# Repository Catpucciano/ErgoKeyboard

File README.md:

<h1 align="center">Catpucciano</h1>

Catpucciano is 34 key key column-staggered choc split keyboard using a SEEED XIAO BLE and inspired by [TOTEM](https://github.com/GEIGEIGEIST/TOTEM/tree/main)

\

---

## Layout

---

## BUILD GUIDE

---

## FILES

### PCB
Gerber Files [Here](/docs/PCB/)
- Download the two zip files and upload them to your choice of manufacture. I used [JLCPCB](https://jlcpcb.com/)
### CASE
Printed in two sections with FDM Printer <br>
3mf for all three files [Case](<./docs/Case Files/Case.3mf>) <br>
[Case](<./docs/Case Files/Case.stl>) <br>
[Top](<./docs/Case Files/Top Case.stl>) <br>
[Top with imbedded Magnets](<./docs/Case Files/Top Magnet.stl>) <br>
[Tenting Case 45 Degrees](<./docs/Case Files/Tenting Case 45.stl>) <br>

---

## FIRMWARE

---

## Credits

### I like the [TOTEM](https://github.com/GEIGEIGEIST/TOTEM/tree/main) by GEIST but not a fan of the splayed layout and wanted something more compact. Having the thumb cluster angled also makes it somewhat awkaward with it sticking out. I removed the upper corner keys to make the keyboard as small as possible to maximize desk space and portability.

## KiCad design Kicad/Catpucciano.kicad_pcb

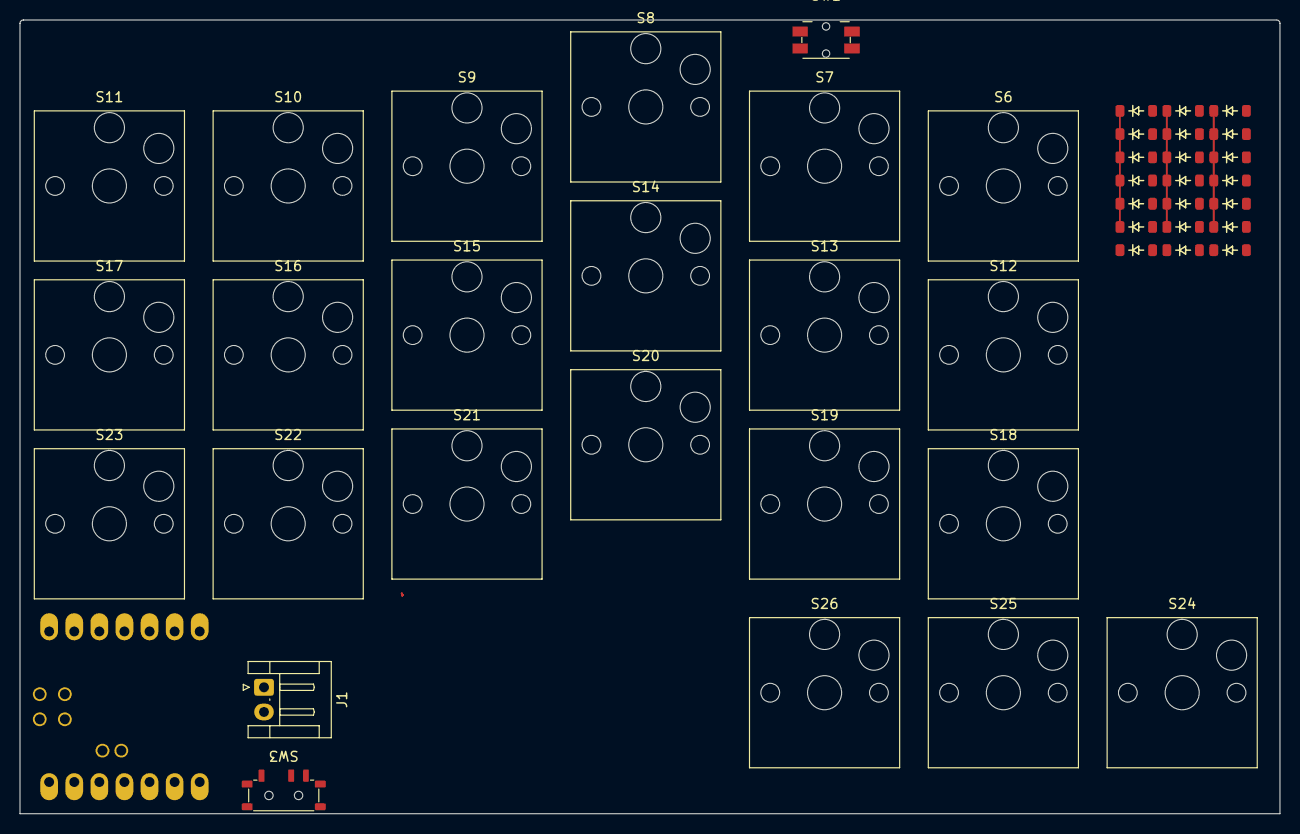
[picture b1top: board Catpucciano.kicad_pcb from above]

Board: 2 copper layers, 127.6 x 80.4 mm, 46 parts (0 on the bottom side), 35 nets.

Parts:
D6, D7, D8, D9, D10, D11, D12, D13, D14, D15, D16, D17, D18, D19, D20, D21, D22, D23, D24, D25, D26: Diode; Diode_SOD-123
J1: Conn_01x02; JST_EH_S2B-EH_1x02_P2.50mm_Horizontal
S6, S7, S8, S9, S10, S11, S12, S13, S14, S15, S16, S17, S18, S19, S20, S21, S22, S23, S24, S25, S26: Keyswitch; Hotswap_Choc_V1_1.00u
SW1: RSW; Panasonic_EVQPUL_EVQPUC
SW3: Switch; Switch_MSK12C02
xiao-ble1: U; xiao-ble-tht

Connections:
BAT+: SW3.1, xiao-ble1.19 (BAT+)
COL0: S6.1, S12.1, S18.1, S24.1, xiao-ble1.6 (A5/05/SCL)
COL1: S7.1, S13.1, S19.1, S25.1, xiao-ble1.7 (Tx/11)
COL2: S8.1, S14.1, S20.1, S26.1, xiao-ble1.8 (Rx/12)
COL3: S9.1, S15.1, S21.1, xiao-ble1.9 (SCK/13)
COL4: S10.1, S16.1, S22.1, xiao-ble1.10 (MISO/14)
COL5: S11.1, S17.1, S23.1, xiao-ble1.11 (MOSI/15)
GND: J1.1, SW1.2, xiao-ble1.13 (GND), xiao-ble1.18 (GND), xiao-ble1.20 (GND)
unnamed: D6.2 (A), S6.2
unnamed: D7.2 (A), S7.2
unnamed: D8.2 (A), S8.2
unnamed: D9.2 (A), S9.2
unnamed: D10.2 (A), S10.2
unnamed: D11.2 (A), S11.2
unnamed: D12.2 (A), S12.2
unnamed: D13.2 (A), S13.2
unnamed: D14.2 (A), S14.2
unnamed: D15.2 (A), S15.2
unnamed: D16.2 (A), S16.2
unnamed: D17.2 (A), S17.2
unnamed: D18.2 (A), S18.2
unnamed: D19.2 (A), S19.2
unnamed: D20.2 (A), S20.2
unnamed: D21.2 (A), S21.2
unnamed: D22.2 (A), S22.2
unnamed: D23.2 (A), S23.2
unnamed: D24.2 (A), S24.2
unnamed: D25.2 (A), S25.2
unnamed: D26.2 (A), S26.2
RESET: SW1.1, xiao-ble1.17 (RST)
ROW1: D6.1 (K), D7.1 (K), D8.1 (K), D9.1 (K), D10.1 (K), D11.1 (K), xiao-ble1.2 (A1/03)
ROW2: D12.1 (K), D13.1 (K), D14.1 (K), D15.1 (K), D16.1 (K), D17.1 (K), xiao-ble1.3 (A2/28)
ROW3: D18.1 (K), D19.1 (K), D20.1 (K), D21.1 (K), D22.1 (K), D23.1 (K), xiao-ble1.4 (A3/29)
ROW4: D24.1 (K), D25.1 (K), D26.1 (K), xiao-ble1.5 (A4/04/SDA)
VBAT: J1.2, SW3.2

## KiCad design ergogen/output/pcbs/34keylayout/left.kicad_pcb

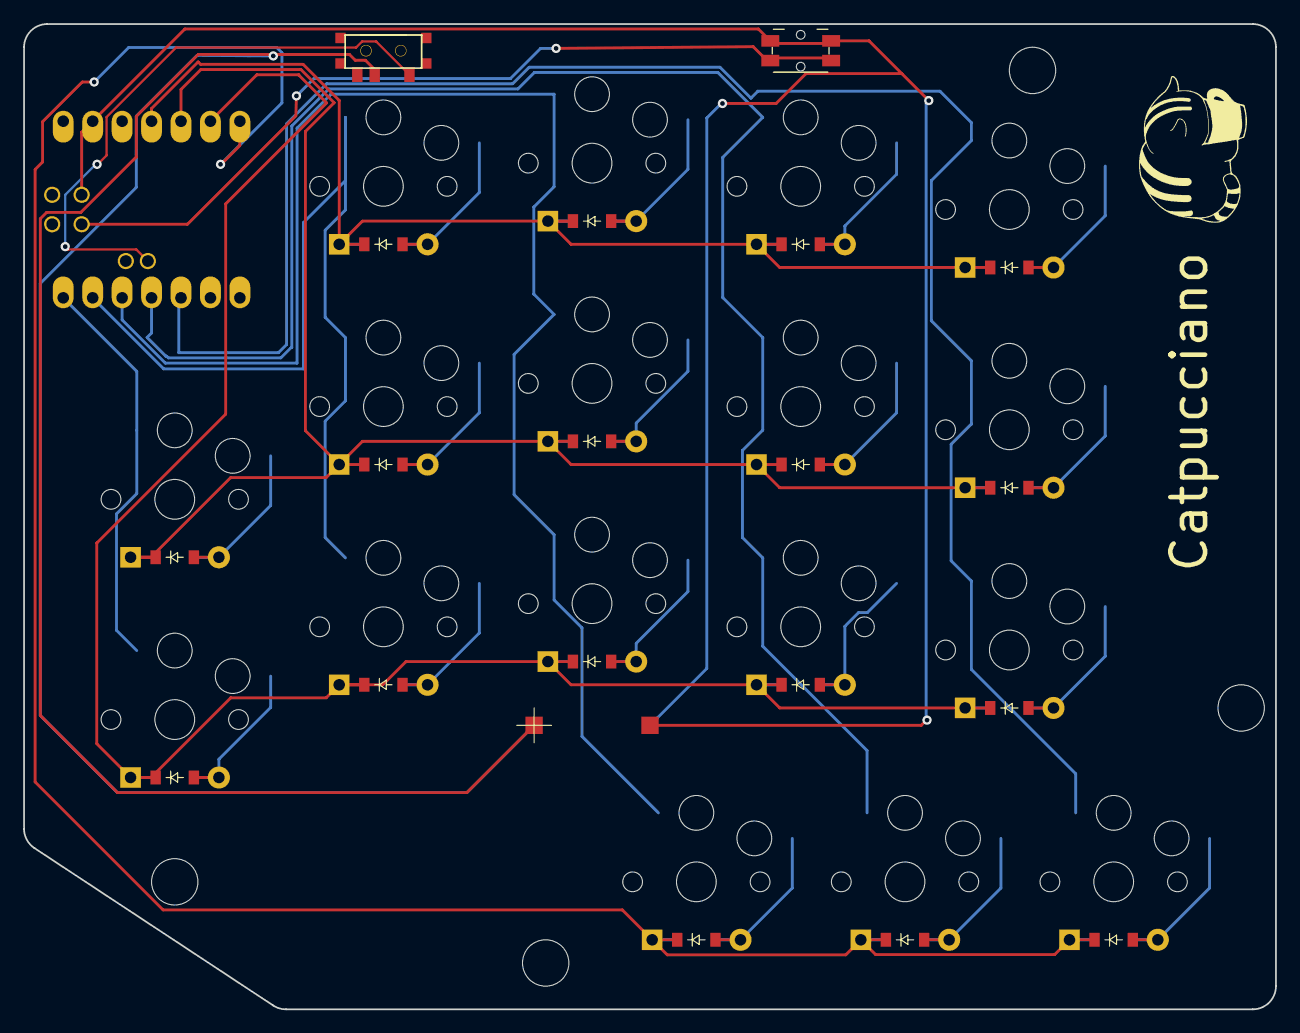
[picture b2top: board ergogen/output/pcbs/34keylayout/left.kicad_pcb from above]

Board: 2 copper layers, 108.0 x 85.0 mm, 38 parts (0 on the bottom side), 30 nets.

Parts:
B1: Panasonic_EVQPUL_EVQPUC
BATTPAD1: ComboDiode
D1, D2, D3, D4, D5, D6, D7, D8, D9, D10, D11, D12, D13, D14, D15, D16, D17: ComboDiode
MCU1: xiao-ble
S1, S2, S3, S4, S5, S6, S7, S8, S9, S10, S11, S12, S13, S14, S15, S16, S17: PG1350
T1: SPDT_C128955

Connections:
BAT+: MCU1.18, T1.1
GND: B1.1, BATTPAD1.2, MCU1.12, MCU1.16
P0: MCU1.6, S1.1, S2.1
P1: MCU1.5, S3.1, S4.1, S5.1
P2: MCU1.4, S6.1, S7.1, S8.1, S15.1
P3: MCU1.3, S9.1, S10.1, S11.1, S16.1
P4: MCU1.2, S12.1, S13.1, S14.1, S17.1
P7: D15.1, D16.1, D17.1, MCU1.7
P8: D1.1, D3.1, D6.1, D9.1, D12.1, MCU1.8
P9: D2.1, D4.1, D7.1, D10.1, D13.1, MCU1.9
P10: D5.1, D8.1, D11.1, D14.1, MCU1.10
POS: BATTPAD1.1, T1.2
RST: B1.2, MCU1.17
index_bottom: D9.2, S9.2
index_clusters: D16.2, S16.2
index_middle: D10.2, S10.2
index_top: D11.2, S11.2
inner_bottom: D12.2, S12.2
inner_clusters: D17.2, S17.2
inner_middle: D13.2, S13.2
inner_top: D14.2, S14.2
middle_bottom: D6.2, S6.2
middle_clusters: D15.2, S15.2
middle_middle: D7.2, S7.2
middle_top: D8.2, S8.2
pinky_bottom: D1.2, S1.2
pinky_middle: D2.2, S2.2
ring_bottom: D3.2, S3.2
ring_middle: D4.2, S4.2
ring_top: D5.2, S5.2

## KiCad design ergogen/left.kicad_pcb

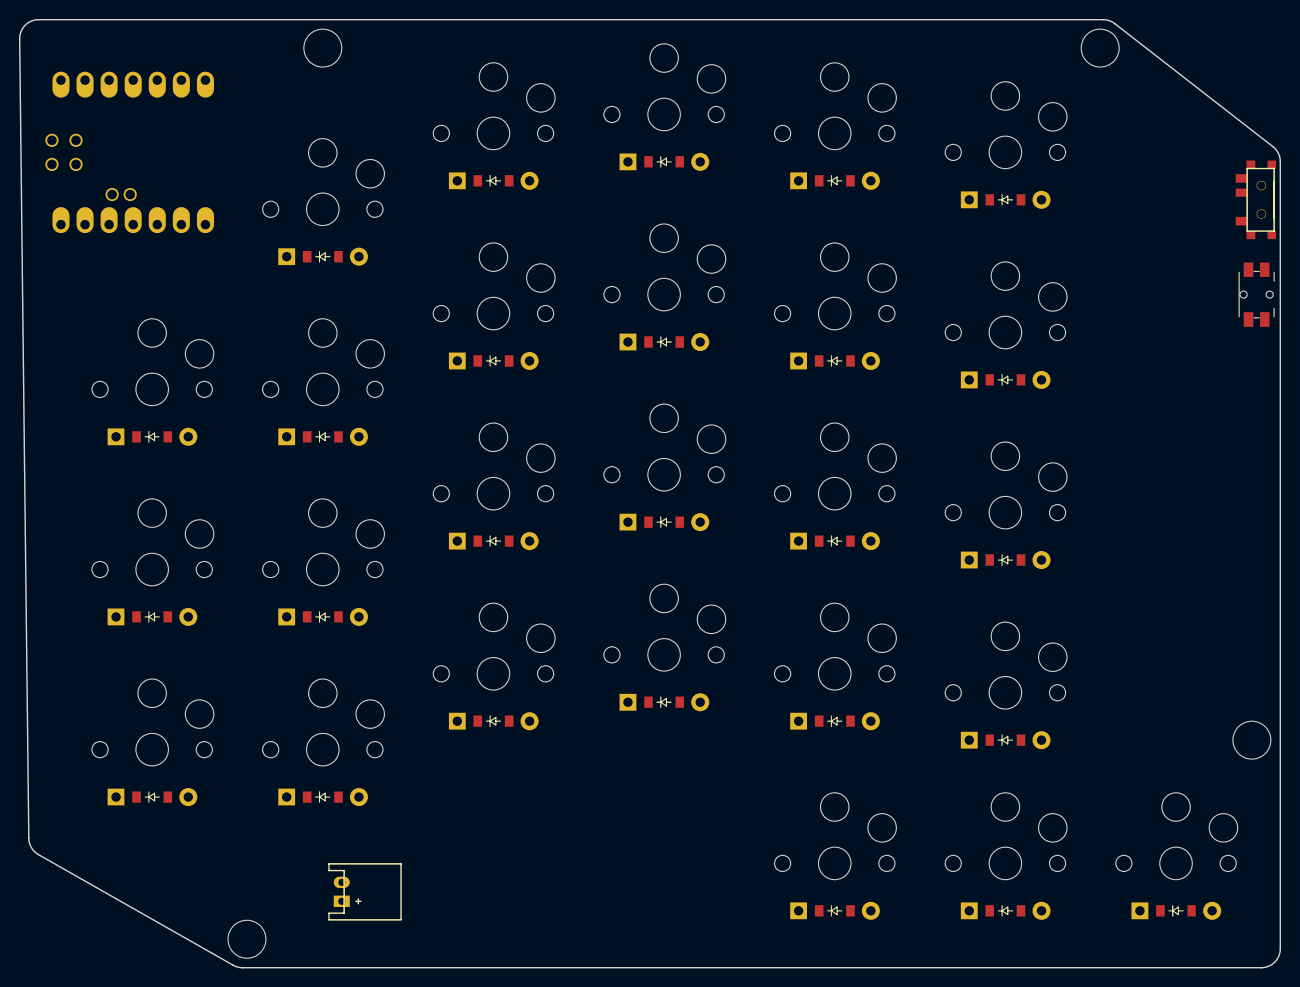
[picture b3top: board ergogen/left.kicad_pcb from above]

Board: 2 copper layers, 133.0 x 100.0 mm, 56 parts (0 on the bottom side), 6 nets, no tracks yet.

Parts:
B1: Panasonic_EVQPUL_EVQPUC
D1, D2, D3, D4, D5, D6, D7, D8, D9, D10, D11, D12, D13, D14, D15, D16, D17, D18, D19, D20, D21, D22, D23, D24, D25, D26: ComboDiode
JST1: JST_PH_S2B-PH-K_02x2.00mm_Angled
MCU1: xiao-ble
S1, S2, S3, S4, S5, S6, S7, S8, S9, S10, S11, S12, S13, S14, S15, S16, S17, S18, S19, S20, S21, S22, S23, S24, S25, S26: PG1350
T1: SPDT_C128955

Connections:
GND: B1.1, JST1.2, MCU1.2, MCU1.17, T1.2
P6: D24.1, D25.1, D26.1, MCU1.8
P7: D1.1, D4.1, D8.1, D12.1, D16.1, D20.1, MCU1.7
P8: D2.1, D5.1, D9.1, D13.1, D17.1, D21.1, MCU1.6
P9: D3.1, D6.1, D10.1, D14.1, D18.1, D22.1, MCU1.5
pos: JST1.1, T1.1

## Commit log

2024-09-17 Uploaded Progress
2024-09-22 Added Nice Nano Footprints & XIAO footprints, mounting hole & reset footprints
2024-09-22 Updated Units, Changed Thumb Clusters to 3 instead of 2, Added in pro micro temporary, Added in JST, Power, Reset, & Mount holes
2024-09-22 Added Other Layouts, Angled Pinky & Ring renamed, Added Version with no numrow
2024-09-22 Started on Seeed XIAO footprint, Added footprint file as well
2024-09-27 Added Completed Xiao Ble footprint
2024-09-27 Added extra footprints for reversible pcb option in future
2024-09-30 Added Keyboard Schematic
2024-09-30 Added Kicad Files
2024-10-24 Added Left Kicad pcb
2024-10-24 Reorganized Files
2024-10-26 Added Alternate Versions
2024-10-27 Added Finished 54 & 34 layouts
2024-10-27 Added Initial Keyboard Firmware
2024-10-27 Added Initial Firmware for Actions
2024-10-27 Added Workflows for Actions
2024-11-15 Fixed gpio pins & Added keymap
2024-11-15 Updated ZMK repo
2024-11-21 Modified west.yml for custom urob functions (zmk-helpers)
2024-11-29 Added Documentation Images
2024-11-29 Added Images to README
2024-11-29 Replaced Heic image with jpg
2024-12-03 Added Case Files
2024-12-03 Update README.md
    Path to Case Files
2024-12-03 Update README.md
    Fixed Readme
2024-12-03 Added PCB Files
2024-12-03 Update README.md
    Link and instruction for pcb downloads
